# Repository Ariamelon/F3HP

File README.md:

# F3HP
A compact, class A amplifier with a schematic from [this](https://www.diyaudio.com/community/threads/3-transistor-hp-amplifier-with-low-dist.359267) thread.
This design uses mostly SMT components with some THT. It is designed to fit in [this](https://item.taobao.com/item.htm?id=543297256145) case. The 3D model and dimensions are included with the design files.

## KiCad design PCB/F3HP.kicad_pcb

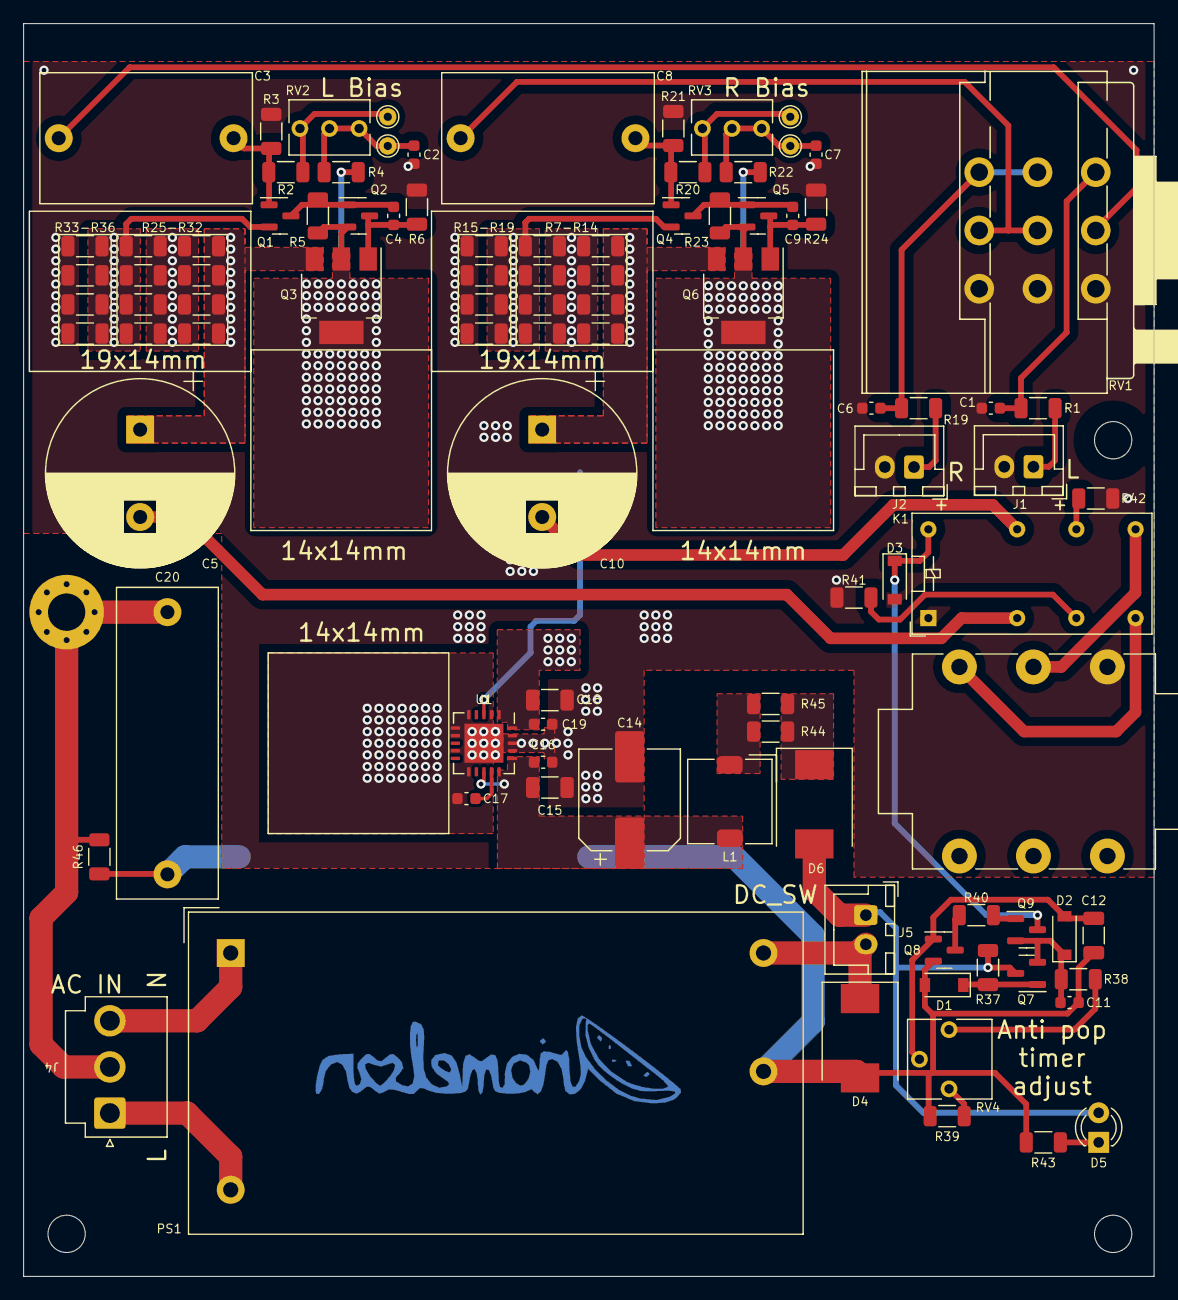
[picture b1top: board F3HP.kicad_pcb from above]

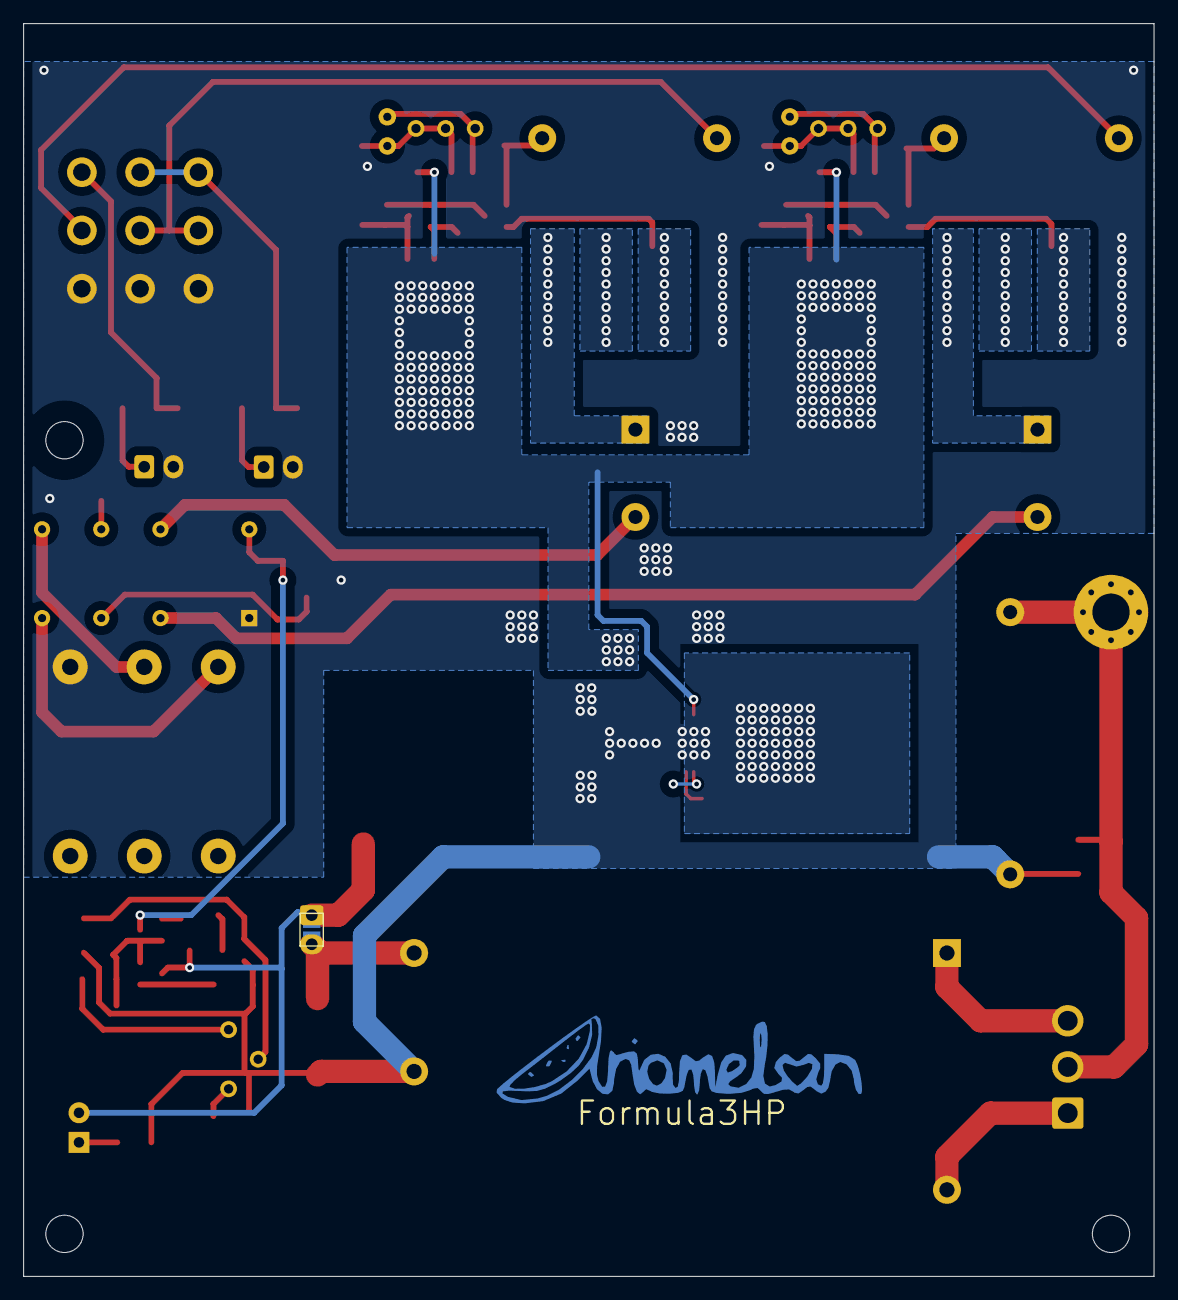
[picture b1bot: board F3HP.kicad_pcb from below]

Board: 2 copper layers, 97.0 x 107.5 mm, 103 parts (2 on the bottom side), 48 nets.

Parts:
A1: Art; Ariamelon_Logo_x3_CU
C1, C6: 100p; C_0603_1608Metric
C2, C7, C11, C16, C19: 10u; C_0603_1608Metric
C3, C8: 2.2u; C_Rect_L18.0mm_W11.0mm_P15.00mm_FKS3_FKP3
C4, C9: 330p; C_0603_1608Metric
C5, C10: 2200u; CP_Radial_D16.0mm_P7.50mm
C12, C15, C18: 47u; C_1206_3216Metric
C14: 470u; CP_Elec_8x10.5
C17: 1u; C_0603_1608Metric
C20: 100n; C_Rect_L26.5mm_W8.5mm_P22.50mm_MKS4
D1: 12V; D_SOD-123
D2, D3: D; D_SOD-123
D4: 15V; D_SMC
D5: LED; LED_D3.0mm
D6: 0.55Vf; D_SMC
H1, H2, H3: MountingHole; MountingHole_3.2mm_M3
H4: Earth; MountingHole_3.2mm_M3_Pad_Via
J1: L_In; JST_XH_B2B-XH-A_1x02_P2.50mm_Vertical
J2: R_In; JST_XH_B2B-XH-A_1x02_P2.50mm_Vertical
J3: HPOut; Jack_6.35mm_Neutrik_NMJ6HCD2_Horizontal
J4: AC_In; JST_VH_B3P-VH_1x03_P3.96mm_Vertical
J5: Switch; JST_XH_B2B-XH-A_1x02_P2.50mm_Vertical
JP1: Switch; SolderJumper-2_P1.3mm_Open_Pad1.0x1.5mm
K1: C93402; Relay_DPDT_Omron_G5V-2
L1: 100u; L_TDK_SLF7032
PS1: RAC20-15SK; Converter_ACDC_Recom_RAC20-xxSK_THT
Q1, Q4, Q7: BC850C; SOT-23
Q2, Q5, Q9: BC860C; SOT-23
Q3, Q6: BCP56TA; SOT-223-3_TabPin2
Q8: AO3400A; SOT-23
R1, R19: 2.2k; R_1206_3216Metric
R2, R20, R38, R39: 390k; R_1206_3216Metric
R3, R21: 120k; R_1206_3216Metric
R4, R22: 39k; R_1206_3216Metric
R5, R23: 820; R_1206_3216Metric
R6, R24: 1.2k; R_1206_3216Metric
R7, R8, R9, R10, R11, R12, R13, R14, R25, R26, R27, R28, R29, R30, R31, R32: 133; R_1206_3216Metric
R15, R16, R17, R18, R33, R34, R35, R36: 93.1; R_1206_3216Metric
R37, R40, R43: 4.7k; R_1206_3216Metric
R41, R42: 1k; R_1206_3216Metric
R44, R45: 1; R_1206_3216Metric
R46: 1M; R_1206_3216Metric
RV1: 50k; ALPS_RK27112
RV2, RV3: 5k; Potentiometer_Bourns_3266Y_Vertical
RV4: 500k; Potentiometer_Vishay_T73YP_Vertical
TP1, TP2, TP3, TP4: TestPoint; TestPoint_THTPad_D1.5mm_Drill0.7mm
U1: TPS7A4701; QFN-20-1EP_5x5mm_P0.65mm_EP3.35x3.35mm

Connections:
+12V: C18.1, C19.1, Q2.2 (E), Q3.2 (C), Q5.2 (E), Q6.2 (C), R4.2, R5.1, R22.2, R23.1, U1.1 (OUT), U1.3 (SENSE/FB), U1.20 (OUT)
+15V: D5.2 (A), D6.2 (A), J5.1, JP1.1, Q7.3 (C), R37.1
GND: C1.1, C2.2, C6.1, C7.2, C11.2, C12.2, C14.2, C15.2, C16.2, C17.2, C18.2, C19.2, C20.1, D1.2 (A), D3.2 (A), D4.2 (A), J1.2, J2.2, J3.S, K1.1, PS1.4 (-Vout), Q8.2 (S), R3.2, R6.2, R15.2, R16.2, R17.2, R18.2, R21.2, R24.2, R33.2, R34.2, R35.2, R36.2, R39.2, R41.1, R42.1, R43.2, R46.1, RV1.1, RV1.4, U1.2 (NC), U1.5 (6P4V1), U1.6 (3P2V), U1.7 (GND), U1.9 (0P8V), U1.11 (0P2V), U1.17 (NC), U1.18 (NC), U1.19 (NC), U1.21 (GND)
GNDPWR: C20.2, H4.1, J4.2, R46.2
L_Out: C5.2, K1.4
unnamed: C1.2, R1.1, RV1.3
unnamed: C2.1, R4.1, RV2.2, RV2.3, TP1.1
unnamed: C3.1, RV1.2
unnamed: C3.2, Q1.1 (B), R2.2, R3.1
unnamed: C4.1, Q2.3 (C), Q3.1 (B), R6.1
unnamed: C4.2, Q1.3 (C), Q2.1 (B), R5.2
unnamed: C5.1, Q3.3 (E), R7.1, R9.1, R11.1, R13.1
unnamed: C6.2, R19.1, RV1.6
unnamed: C7.1, R22.1, RV3.2, RV3.3, TP3.1
unnamed: C8.1, RV1.5
unnamed: C8.2, Q4.1 (B), R20.2, R21.1
unnamed: C9.1, Q5.3 (C), Q6.1 (B), R24.1
unnamed: C9.2, Q4.3 (C), Q5.1 (B), R23.2
unnamed: C10.1, Q6.3 (E), R25.1, R27.1, R29.1, R31.1
unnamed: C11.1, D2.1 (K), Q7.2 (E), Q9.2 (E), R38.1
unnamed: C12.1, D2.2 (A), Q8.1 (G), RV4.2
unnamed: C14.1, C15.1, C16.1, L1.2, U1.13 (EN), U1.15 (IN), U1.16 (IN)
unnamed: C17.1, U1.14 (NR)
unnamed: D1.1 (K), Q7.1 (B), R37.2
unnamed: D3.1 (K), K1.16, Q9.3 (C)
unnamed: D4.1 (K), J5.2, JP1.2, PS1.5 (+Vout)
unnamed: D5.1 (K), R43.1
unnamed: D6.1 (K), R44.1, R45.1
unnamed: J1.1, R1.2
unnamed: J2.1, R19.2
unnamed: J3.R, K1.9
unnamed: J3.T, K1.8
unnamed: J4.1, PS1.2 (AC(L))
unnamed: J4.3, PS1.1 (AC(N))
unnamed: K1.6, R41.2
unnamed: K1.11, R42.2
unnamed: L1.1, R44.2, R45.2
unnamed: Q1.2 (E), R8.2, R10.2, R12.2, R14.2, R15.1, R16.1, R17.1, R18.1
unnamed: Q4.2 (E), R26.2, R28.2, R30.2, R32.2, R33.1, R34.1, R35.1, R36.1
unnamed: Q8.3 (D), R40.1
unnamed: Q9.1 (B), R40.2
unnamed: R2.1, RV2.1, TP2.1
unnamed: R7.2, R8.1, R9.2, R10.1, R11.2, R12.1, R13.2, R14.1
unnamed: R20.1, RV3.1, TP4.1
unnamed: R25.2, R26.1, R27.2, R28.1, R29.2, R30.1, R31.2, R32.1
unnamed: R38.2, RV4.1
unnamed: R39.1, RV4.3
R_Out: C10.2, K1.13

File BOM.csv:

Qty,Reference(s),Value,LCSC part number,Part number
2,"C1, C6",100p,C343033,C1608NP01H101JT000N
5,"C2, C7, C11, C16, C19",10u,C962136,CL10A106KO8NQNC
2,"C3, C8",2.2u,C128507,ECWFD2W225J
2,"C4, C9",330p,C343002,C1608NP01H331JT000N
2,"C5, C10",2200u,C278533,EEUFR1E222S
3,"C12, C15, C18",47u,C385907,EMK316BBJ476ML-T
1,C14,470u,,
1,C17,1u,C962136,CL10A106KO8NQNC
1,C20,100n,C2926846,PHE820ED6100MR06L2
1,D1,12V,C550177,BZT52-B12X
2,"D2, D3",D,C81598,1N4148W
1,D4,15V,C135138,SMCJ15A-13-F
1,D5,LED,C2927624,204-10SUGC/S400-A5
1,D6,0.55Vf,C134460,B520C-13-F
1,J1,L_In,C158012,B2B-XH-A
1,J2,R_In,C158012,B2B-XH-A
1,J3,HPOut,C368502,NMJ6HCD2
1,J4,AC_In,C160316,B3P-VH(LF)(SN)
1,J5,Switch,C158012,B2B-XH-A
1,K1,C93402,C128021,C93402
1,L1,100u,C2045491,SPM7054VT-101M-D
1,PS1,RAC20-15SK,N/A,RAC20-15SK
3,"Q1, Q4, Q7",BC850C,C549507,BC850C
3,"Q2, Q5, Q9",BC860C,C549546,BC860C
2,"Q3, Q6",BCP56TA,C177012,BCP56TA
1,Q8,AO3400A,C20917,AO3400A
2,"R1, R19",2.2k,C706068,RT0603DRE072K2L
4,"R2, R20, R38, R39",390k,C862701,RT0603DRD07390KL
2,"R3, R21",120k,C706020,RT0603DRE07120KL
2,"R4, R22",39k,C705983,RT0603DRD0739RL
2,"R5, R23",820,C723589,RT0603DRD07820RL
2,"R6, R24",1.2k,C723656,RT0603DRD071K2L
16,"R7, R8, R9, R10, R11, R12, R13, R14, R25, R26, R27, R28, R29, R30, R31, R32",133,C872564,RT1206DRD07133RL
8,"R15, R16, R17, R18, R33, R34, R35, R36",93.1,C706437,RT1206FRE0793R1L
3,"R37, R40, R43",4.7k,C513565,RT0603BRD074K7L
2,"R41, R42",1k,C706049,RT0603DRE071KL
2,"R44, R45",1,C728690,RT1206FRE071RL
1,R46,1M,C862961,RT0603DRE071ML
1,RV1,50k,C470507,RK27112A00AK
2,"RV2, RV3",5k,C780226,3266W-1-503LF
1,RV4,500k,C125021,3362P-1-504
1,U1,TPS7A4701,C68214,TPS7A4701
,,,,
Additional,,,,
1,,IEC socket,N/A,DD11.0111.1111
1,,Fuse holder,N/A,4301.1405
1,,Power switch,C1788492,100SP1T1B1M1QEH
1,,JST VH plug,C157899,VHR-3N
3,,JST VH pins,C160349,SVH-21T-P1.1
3,,JST XH plug,C144401,XHP-2
6,,JST XH pins,C385122,SXH-001T-P0.6N
1,,RCA black,N/A,NYS367-0
1,,RCA red,N/A,NYS367-2
1,,30mm knob,N/A,N/A
1,,200mA slow blow,C178874,0218.200MXP
4,,M3 x 6,,Normal screw
5,,M3 x 6,,Countersunk screw
3,,14 x 14mm,C286220,Heatsink
1,,22 x 22mm,C286191,Heatsink

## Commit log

2022-06-05 Better layout, better heatsinking
2022-06-07 Updated component values and BOM
2022-06-08 Swapped to TPS7A4701 LDO, better performance and less complicated PCB required
2022-06-08 Errors fixed
2022-06-09 Added back LC filter after ACDC converter
2022-06-09 Added Alps RK163 support
2022-06-13 Changed resistors to 1206 to lower distortion
